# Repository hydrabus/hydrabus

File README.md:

HydraBus
========

HydraBus an open source multi-tool hardware

You can Buy HydraBus/HydraNFC Online: http://hydrabus.com/buy-online

Wiki Getting Started: https://github.com/hydrabus/hydrafw/wiki/Getting-Started-with-HydraBus

HydraFW official firmware for Hydrabus
========

Wiki for HydraFW: https://github.com/hydrabus/hydrafw/wiki

See https://github.com/hydrabus/hydrafw

To build hydrafw see instructions here: 
* Windows: https://github.com/hydrabus/hydrafw/wiki/how-to-build-flash-and-use-hydrafw-on-windows
* Linux: https://github.com/hydrabus/hydrafw/wiki/how-to-build-flash-and-use-hydrafw-on-linux

Official Micro Python port for HydraBus
========
See https://github.com/micropython/micropython
Tested with GCC ARM 4.9 2015q3(GNU_ARM_4_9_2015q3) 
* See https://github.com/hydrabus/hydrafw_hydranfc_shield_v2/wiki `How to Build/Flash/Use HydraFW` for more details

To build micropython for HydraBus do:

    git clone --recursive https://github.com/micropython/micropython
    cd micropython/ports/stm32
    make BOARD=HYDRABUS

* At end of build you shall have:
 * GEN build-HYDRABUS/firmware.dfu
 * GEN build-HYDRABUS/firmware.hex
* In order to flash the *.dfu follow steps here: https://github.com/hydrabus/hydrafw/wiki/Getting-Started-with-HydraBus

For more details on official micropython hydrabus port see: https://github.com/micropython/micropython/tree/master/ports/stm32/boards/HYDRABUS

Official Black Magic JTAG/SWD debugger port for HydraBus
========
See https://github.com/blacksphere/blackmagic.git

Before to build the firmware check this issue (as you need a new GCC ARM Compiler >=4.9): https://github.com/blacksphere/blackmagic/issues/128
Tested with GCC ARM 4.9 2015q3(GNU_ARM_4_9_2015q3)
* See working version for reference blackmagic_branch_hydrabus_Firmware 1.5-00319-g49390fe-dirty.zip:
  * https://github.com/hydrabus/hydrabus/files/11436416/blackmagic_branch_hydrabus_Firmware.1.5-00319-g49390fe-dirty.zip
* Note: Latest version of blackmagic have "Device failed enumeration" issue see https://github.com/hydrabus/hydrabus/issues/4
* See https://github.com/hydrabus/hydrafw_hydranfc_shield_v2/wiki `How to Build/Flash/Use HydraFW` for more details

To build Black Magic for HydraBus do:

    git clone --recursive https://github.com/blacksphere/blackmagic.git
    cd blackmagic
    make PROBE_HOST=hydrabus

* At end of build you shall have:
 * OBJCOPY blackmagic.bin
 * OBJCOPY blackmagic.hex
 * Creating blackmagic.dfu
* In order to flash the *.dfu follow steps here: https://github.com/bvernoux/hydrafw/wiki/Getting-Started-with-HydraBus

For more details on official blackmagic hydrabus port see:
https://github.com/blacksphere/blackmagic/tree/master/src/platforms/hydrabus

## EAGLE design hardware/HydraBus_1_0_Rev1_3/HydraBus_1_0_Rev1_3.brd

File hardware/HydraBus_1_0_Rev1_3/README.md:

HydraBus Schematic and Board CadSoft Eagle 6.x
========

This directory contains HydraBus Schematic and Board for CadSoft Eagle 6.x (free version works too)

HydraBus: Hardware license [CC BY-NC 4.0](https://creativecommons.org/licenses/by-nc/4.0/) (for commercial license contact info@hydrabus.com)

For more details on the hardware see also http://hydrabus.com/hydrabus-1-0-specifications

Revision 1.3 (vs Rev 1.2+)
- Modified the 2 microUSB to new ones which are more robust (HRO_U-F-M5DD-Y-L)
- Minor board routing improvement/optimization

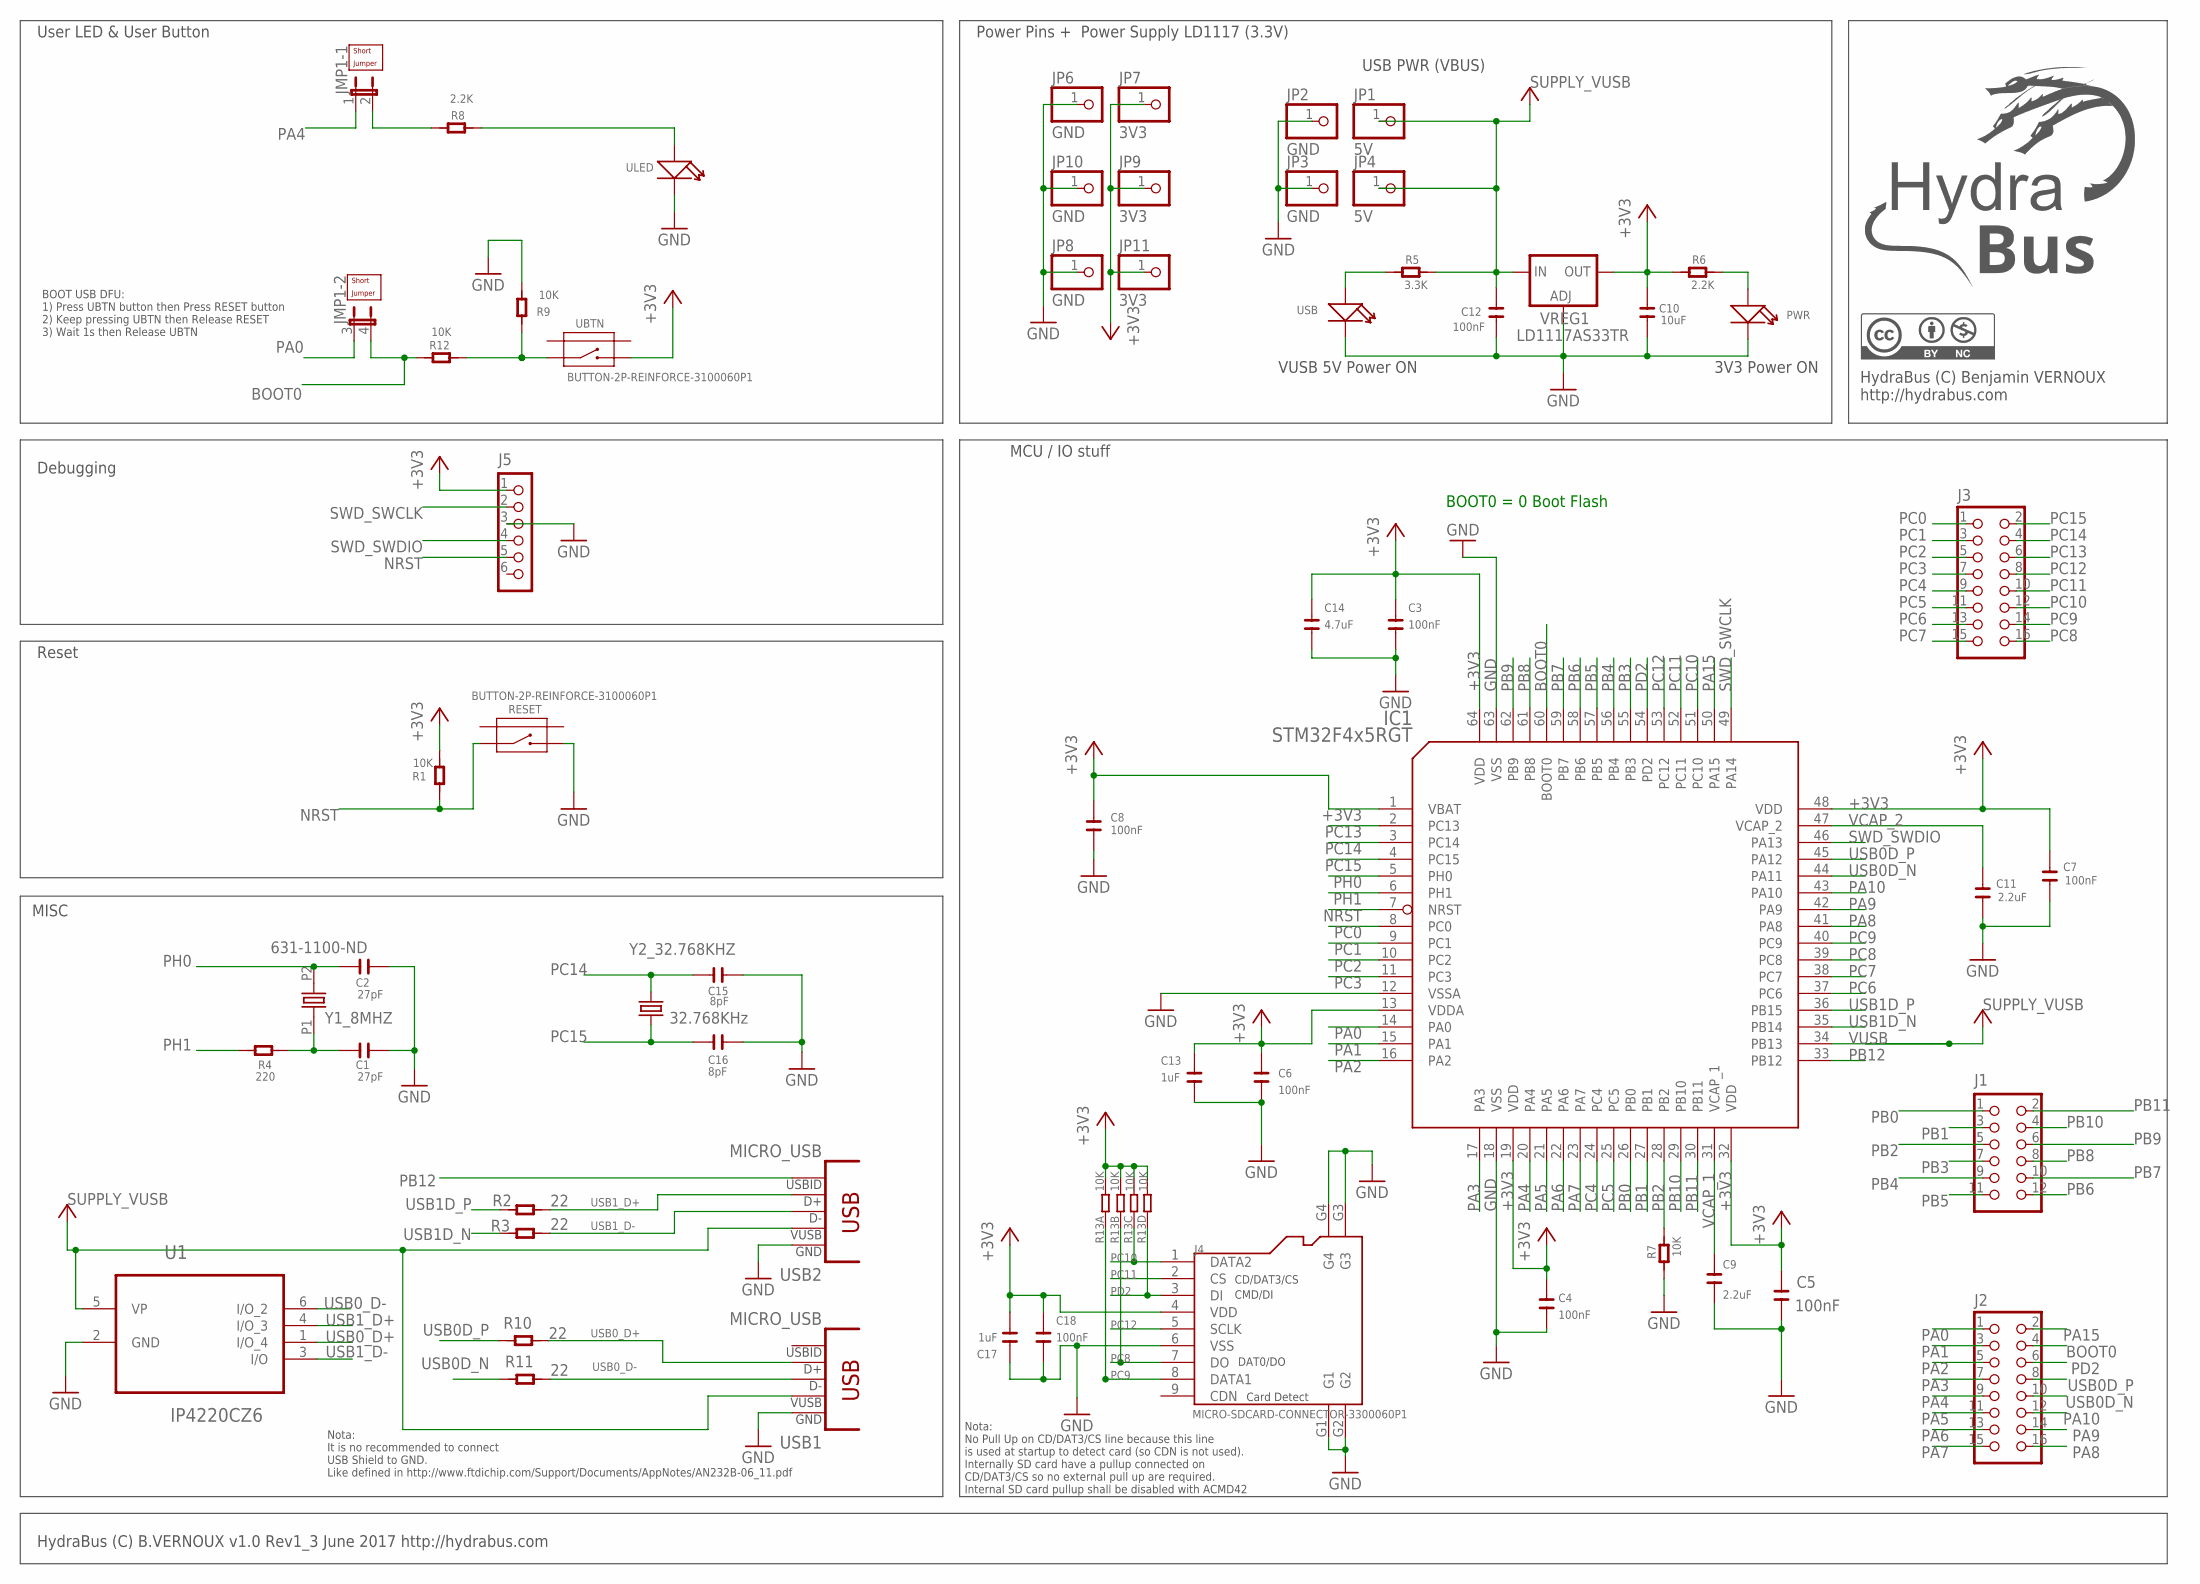
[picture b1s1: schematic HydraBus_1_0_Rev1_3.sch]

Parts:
C1, C2: 27pF; C0603
C3, C4, C5, C6, C7, C8, C12, C18: 100nF; C0603
C9, C11: 2.2uF; C0603
C10: 10uF; C0805
C13, C17: 1uF; C0603
C14: 4.7uF; C0603
C15, C16: 8pF; C0603
IC1: STM32F4x5RGT; LQFP64
J1: CON_HEADER_2X06; M2X6
J2, J3: CON_HEADER_2X08; M2X8
J4: MICRO-SDCARD-CONNECTOR-3300060P1; 9P-SMD-W-RING
J5: CON_HEADER_1X06-PTH; M1X6
JMP1: JP2QE; JP2Q
JMP_UBTN: SHORT-JUMPER-2P-3460440P1; 2P-2.54
JMP_ULED: SHORT-JUMPER-2P-3460440P1; 2P-2.54
JP1, JP4: 5V; 1X01
JP2, JP3, JP6, JP8, JP10: GND; 1X01
JP7, JP9, JP11: 3V3; 1X01
PWR: LED; LED0603
R1, R7, R9, R12: 10K; R0603
R2, R3, R10, R11: 22; R0603
R4: 220; R0603
R5: 3.3K; R0603
R6, R8: 2.2K; R0603
R13: 10K; R1206-8
RESET: BUTTON-2P-REINFORCE-3100060P1; 4P-SMD-7.0X3.5X3.5H-90D
U1: IP4220CZ6; SOT95P275X110-6N
UBTN: BUTTON-2P-REINFORCE-3100060P1; 4P-SMD-7.0X3.5X3.5H-90D
ULED: LED; LED0603
USB: LED; LED0603
USB1, USB2: MICRO_USB; MICRO_USB5+6P_SMD_0_65
VREG1: LD1117AS33TR; SOT223
Y1_8MHZ: 631-1100-ND; HC-49U-PTH
Y2_32.768KHZ: 32.768KHz; TC38H

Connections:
+3V3: C3.1, C4.1, C5.2, C6.1, C7.1, C8.1, C10.1, C13.1, C14.1, C17.2, C18.1, IC1.1 (VBAT), IC1.13 (VDDA), IC1.19 (VDD), IC1.32 (VDD), IC1.48 (VDD), IC1.64 (VDD), J4.4 (VDD), J5.1, JP7.1, JP9.1, JP11.1, R1.2, R6.2, R13.5 (2), R13.6 (2), R13.7 (2), R13.8 (2), UBTN.2, VREG1.4 (OUT)
BOOT0: IC1.60 (BOOT0), J2.4, JMP1.4 (2), R12.2
GND: C1.2, C2.2, C3.2, C4.2, C5.1, C6.2, C7.2, C8.2, C9.1, C10.2, C11.2, C12.2, C13.2, C14.2, C15.2, C16.2, C17.1, C18.2, IC1.12 (VSSA), IC1.18 (VSS), IC1.63 (VSS), J4.6 (VSS), J4.G1, J4.G2, J4.G3, J4.G4, J5.3, JP2.1, JP3.1, JP6.1, JP8.1, JP10.1, PWR.-, R7.2, R9.2, RESET.2, U1.2 (GND), ULED.-, USB.-, USB1.5 (GND), USB2.5 (GND), VREG1.1 (ADJ)
unnamed: C1.1, R4.1, Y1_8MHZ.P1 (1)
unnamed: JMP1.2, R8.2
unnamed: R9.1, R12.1, UBTN.1
unnamed: R8.1, ULED.+
unnamed: R5.2, USB.+
unnamed: PWR.+, R6.1
NRST: IC1.7 (NRST), J5.5, R1.1, RESET.1
PA0: IC1.14 (PA0), J2.1, JMP1.3 (1)
PA1: IC1.15 (PA1), J2.3
PA2: IC1.16 (PA2), J2.5
PA3: IC1.17 (PA3), J2.7
PA4: IC1.20 (PA4), J2.9, JMP1.1
PA5: IC1.21 (PA5), J2.11
PA6: IC1.22 (PA6), J2.13
PA7: IC1.23 (PA7), J2.15
PA8: IC1.41 (PA8), J2.16
PA9: IC1.42 (PA9), J2.14
PA10: IC1.43 (PA10), J2.12
PA15: IC1.50 (PA15), J2.2
PB0: IC1.26 (PB0), J1.1
PB1: IC1.27 (PB1), J1.3
PB2: IC1.28 (PB2), J1.5, R7.1
PB3: IC1.55 (PB3), J1.7
PB4: IC1.56 (PB4), J1.9
PB5: IC1.57 (PB5), J1.11
PB6: IC1.58 (PB6), J1.12
PB7: IC1.59 (PB7), J1.10
PB8: IC1.61 (PB8), J1.8
PB9: IC1.62 (PB9), J1.6
PB10: IC1.29 (PB10), J1.4
PB11: IC1.30 (PB11), J1.2
PB12: IC1.33 (PB12), USB2.4 (USBID)
PC0: IC1.8 (PC0), J3.1
PC1: IC1.9 (PC1), J3.3
PC2: IC1.10 (PC2), J3.5
PC3: IC1.11 (PC3), J3.7
PC4: IC1.24 (PC4), J3.9
PC5: IC1.25 (PC5), J3.11
PC6: IC1.37 (PC6), J3.13
PC7: IC1.38 (PC7), J3.15
PC8: IC1.39 (PC8), J3.16, J4.7 (DO), R13.2 (1)
PC9: IC1.40 (PC9), J3.14, J4.8 (DATA1), R13.1
PC10: IC1.51 (PC10), J3.12, J4.1 (DATA2), R13.3 (1)
PC11: IC1.52 (PC11), J3.10, J4.2 (CS)
PC12: IC1.53 (PC12), J3.8, J4.5 (SCLK)
PC13: IC1.2 (PC13), J3.6
PC14: C15.1, IC1.3 (PC14), J3.4, Y2_32.768KHZ.2
PC15: C16.1, IC1.4 (PC15), J3.2, Y2_32.768KHZ.1
PD2: IC1.54 (PD2), J2.6, J4.3 (DI), R13.4 (1)
PH0: C2.1, IC1.5 (PH0), Y1_8MHZ.P2 (2)
PH1: IC1.6 (PH1), R4.2
SWD_SWCLK: IC1.49 (PA14), J5.2
SWD_SWDIO: IC1.46 (PA13), J5.4
USB0D_N: IC1.44 (PA11), J2.10, R11.2
USB0D_P: IC1.45 (PA12), J2.8, R10.2
USB0_D+: R10.1, U1.1 (I/O_4), USB1.3 (D+)
USB0_D-: R11.1, U1.6 (I/O_2), USB1.2 (D-)
USB1D_N: IC1.35 (PB14), R3.2
USB1D_P: IC1.36 (PB15), R2.2
USB1_D+: R2.1, U1.4 (I/O_3), USB2.3 (D+)
USB1_D-: R3.1, U1.3 (I/O), USB2.2 (D-)
VCAP_1: C9.2, IC1.31 (VCAP_1)
VCAP_2: C11.1, IC1.47 (VCAP_2)
VUSB: C12.1, IC1.34 (PB13), JP1.1, JP4.1, R5.1, U1.5 (VP), USB1.1 (VUSB), USB2.1 (VUSB), VREG1.3 (IN)

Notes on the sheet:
Debugging
Power Pins + Power Supply LD1117 (3.3V)
MCU / IO stuff
MISC
Reset
BOOT0 = 0 Boot Flash
USB PWR (VBUS)
3V3 Power ON
VUSB 5V Power ON
HydraBus (C) B.VERNOUX v1.0 Rev1_3 June 2017 http://hydrabus.com
User LED & User Button
CD/DAT3/CS
CMD/DI
Card Detect
DAT0/DO
Nota: No Pull Up on CD/DAT3/CS line because this line is used at startup to detect card (so CDN is not used). Internally SD card have a pullup connected on CD/DAT3/CS so no external pull up are required. Internal SD card pullup shall be disabled with ACMD42
HydraBus (C) Benjamin VERNOUX http://hydrabus.com
Nota: It is no recommended to connect USB Shield to GND. Like defined in http://www.ftdichip.com/Support/Documents/AppNotes/AN232B-06_11.pdf
BOOT USB DFU: 1) Press UBTN button then Press RESET button 2) Keep pressing UBTN then Release RESET 3) Wait 1s then Release UBTN

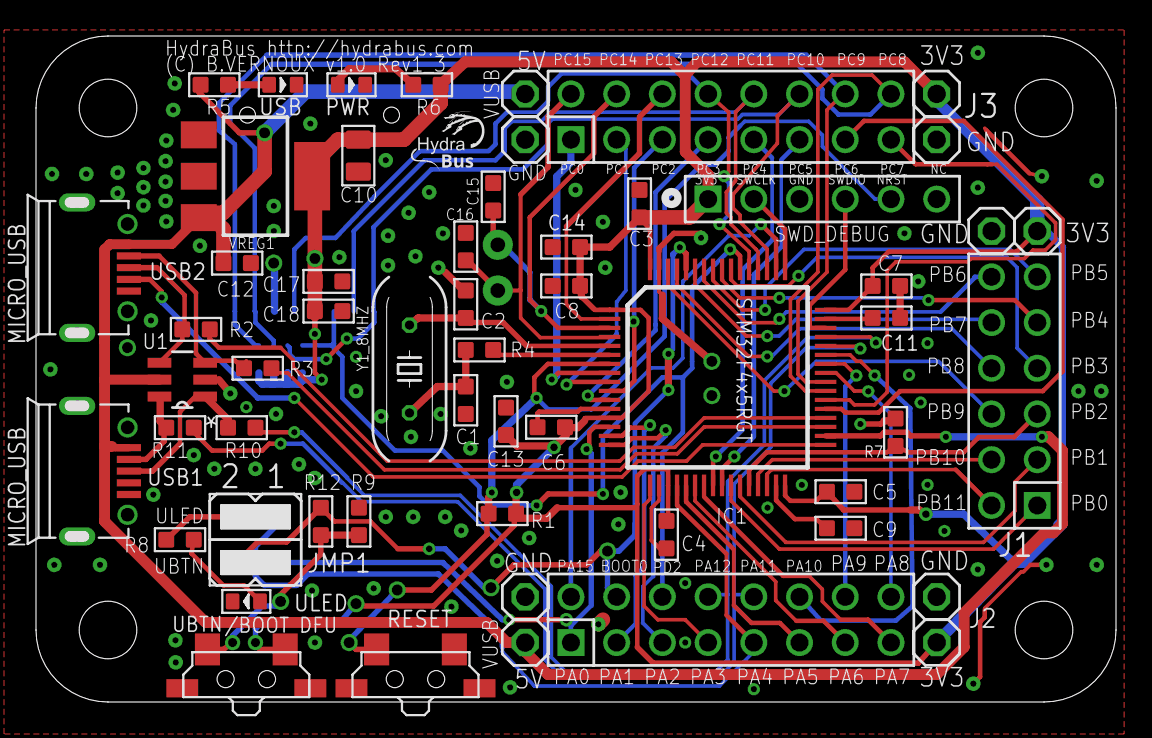
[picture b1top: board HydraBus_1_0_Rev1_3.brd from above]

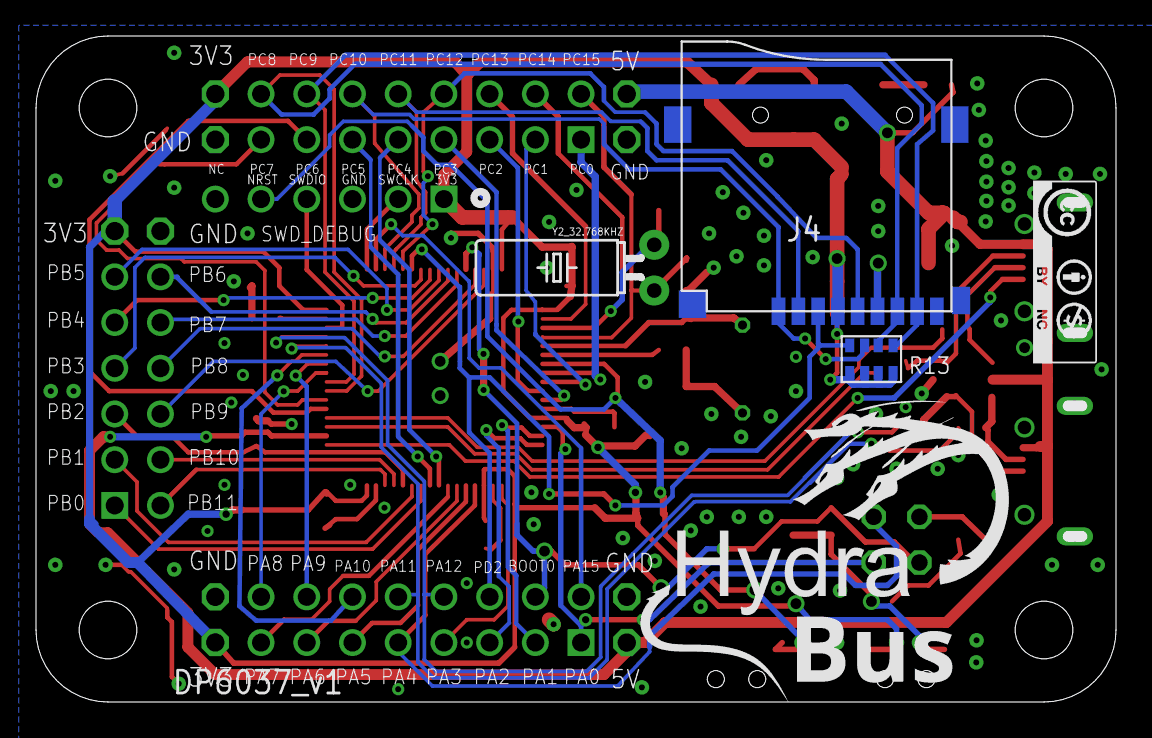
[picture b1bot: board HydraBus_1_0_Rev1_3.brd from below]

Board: 2 copper layers, 59.4 x 36.4 mm, 62 parts (3 on the bottom side), 67 nets.

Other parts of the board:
U$1: DP6037_V1

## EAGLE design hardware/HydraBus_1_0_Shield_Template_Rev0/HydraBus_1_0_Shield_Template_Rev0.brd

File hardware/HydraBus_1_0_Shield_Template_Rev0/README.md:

HydraBus 1_0 Shield Template CadSoft Eagle 6.x
========

This directory contains open source HydraBus 1_0 Shield Template Schematic and Board for CadSoft Eagle 6.x (free version works too)

HydraBus 1_0 Shield Template: Hardware licence CC BY-SA 4.0

For more details on the hardware see also http://hydrabus.com/?page_id=30

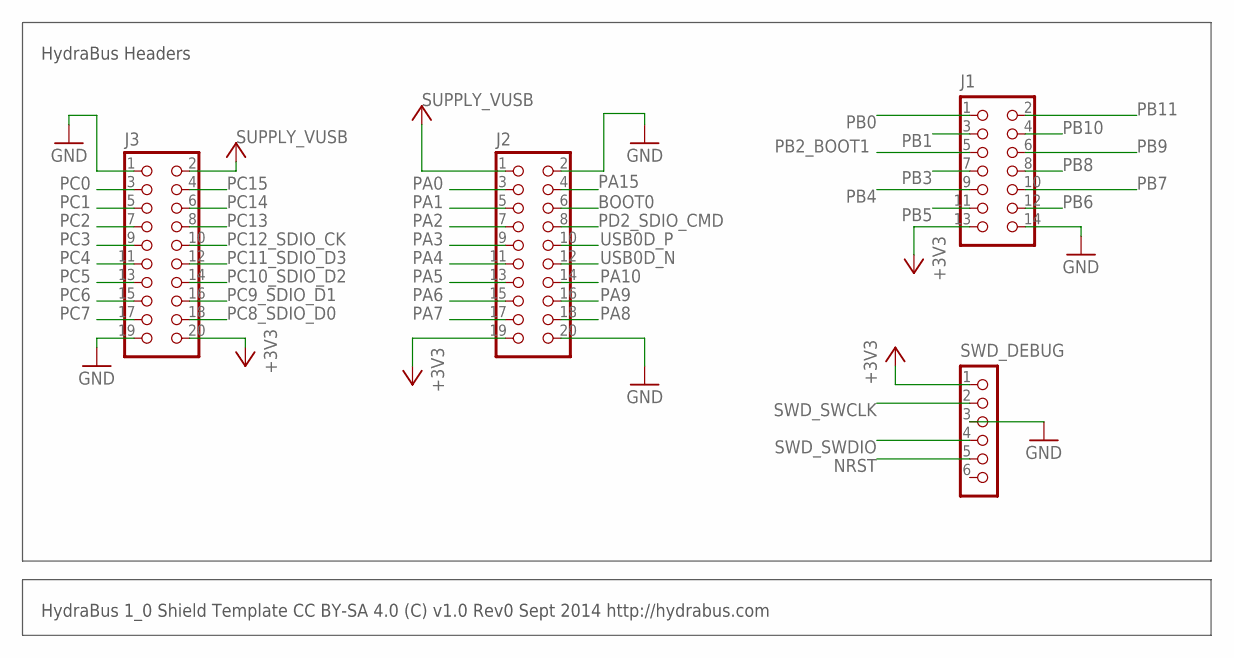
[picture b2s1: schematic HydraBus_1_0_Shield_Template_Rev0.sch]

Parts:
J1: HYDRABUS_SHIELD_CON_HEADER_2X07; HYDRABUS_SHIELD_M2X7
J2, J3: HYDRABUS_SHIELD_CON_HEADER_2X10; HYDRABUS_SHIELD_M2X10
SWD_DEBUG: HYDRABUS_SHIELD_CON_HEADER_1X06; HYDRABUS_SHIELD_M1X6

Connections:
+3V3: J1.13, J2.19, J3.20, SWD_DEBUG.1
BOOT0: J2.6
GND: J1.14, J2.2, J2.20, J3.1, J3.19, SWD_DEBUG.3
NRST: SWD_DEBUG.5
PA0: J2.3
PA1: J2.5
PA2: J2.7
PA3: J2.9
PA4: J2.11
PA5: J2.13
PA6: J2.15
PA7: J2.17
PA8: J2.18
PA9: J2.16
PA10: J2.14
PA15: J2.4
PB0: J1.1
PB1: J1.3
PB2_BOOT1: J1.5
PB3: J1.7
PB4: J1.9
PB5: J1.11
PB6: J1.12
PB7: J1.10
PB8: J1.8
PB9: J1.6
PB10: J1.4
PB11: J1.2
PC0: J3.3
PC1: J3.5
PC2: J3.7
PC3: J3.9
PC4: J3.11
PC5: J3.13
PC6: J3.15
PC7: J3.17
PC8_SDIO_D0: J3.18
PC9_SDIO_D1: J3.16
PC10_SDIO_D2: J3.14
PC11_SDIO_D3: J3.12
PC12_SDIO_CK: J3.10
PC13: J3.8
PC14: J3.6
PC15: J3.4
PD2_SDIO_CMD: J2.8
SWD_SWCLK: SWD_DEBUG.2
SWD_SWDIO: SWD_DEBUG.4
USB0D_N: J2.12
USB0D_P: J2.10
VUSB: J2.1, J3.2

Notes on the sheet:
HydraBus 1_0 Shield Template CC BY-SA 4.0 (C) v1.0 Rev0 Sept 2014 http://hydrabus.com
HydraBus Headers

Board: 2 copper layers, 4 parts (0 on the bottom side), 3 nets, no tracks yet.

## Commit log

2014-04-20 gitmodules update
2014-05-28 Update gitmodules
2014-05-28 Cleanup
2014-05-28 Cleanup gitmodule and added chibios 2.6.x
2014-06-02 HydraBus board
2014-06-22 Moved project/firmware to firmware directory
2014-09-11 HydraBus hardware files Eagle, PDF, xls ...
2014-09-11 Added MicroPython binary for HydraBus and instructions to flash it through USB DFU on HydraBus.
2014-09-11 Added board
2014-09-21 HydraFW first import version 0.1Beta
2014-09-21 Add picture for HydraBus to enter in USB DFU mode
2014-09-29 Update firmware from with last commit https://github.com/bvernoux/micropython/commit/41249e17c3a661dc36f49ff6156ce67a70466157
2014-09-30 HydraBus1.0 Sick Of Beige Case
2014-09-30 Windows XP, Vista, 7 and 8 drivers for HydraBus firmware USB CDC Virtual Serial Port.
2014-09-30 HydraBus1.0 Pin & Pin Assignment updated.
2014-10-01 Fix typo
2014-10-02 Added HydraBus Pins Assignment
2014-10-06 Add micropython firmware source as submodule.
2014-10-06 Add micropython firmware source as submodule and update with latest micropython.
2014-10-06 Cleanup Submodule micropython
2014-10-06 Add latest micropython as submodule
2014-10-06 Update micropython firmware to latest v1.3.3-31-g9c6f737
2014-10-07 Fixo typo thanks to Philippe Teuwen
    Update towards Philippe Teuwen wiki
    http://wiki.yobi.be/wiki/HydraNFC
2014-10-07 Fix for Debian... also exclude ModemManager thanks to Philippe Teuwen
2014-10-07 Fix typo thanks to Philippe Teuwen
    Update towards http://wiki.yobi.be/wiki/HydraNFC "Getting ready to use HydraBus" & "Using HydraBus"
2014-10-08 Cleanup, update configuration/conf and update microrl submodule.
2014-10-09 directory hydrafw deleted/replaced by submodule hydrafw
2014-10-10 Update hydrafw
2014-10-11 Added link to Wiki HydraFW
2014-10-13 Removed STM32F4_USB_DFU_Driver.zip
2014-10-22 Added HydraBus_1_0_HydraFW_Default_PinAssignment.odg/.pdf Fixed and update of HydraBus_1_0_PinAssignment.odg/.pdf
2014-10-22 Add A4 version of HydraBus_1_0_HydraFW_Default_PinAssignment
2014-10-22 Update link to latest hydrafw
2014-10-22 Updated submodule micropython to latest version
2014-10-22 update micropython firmware.dfu to latest version => Micro Python v1.3.3-113-g5fc42a6
2014-12-01 Added HydraBus Basic Pin Assignment
2014-12-26 Update micropython to latest Micro Python v1.3.3-340-gc55a4d8
2014-12-26 Update micropython to latest Micro Python v1.3.7-96-gc55a4d8
2014-12-26 Update hydrafw to latest version v0.4-beta-23-ge68b10a
2015-01-01 Updated Default Pin Assignment A4 and removed the old not A4.
2015-01-13 Added blackmagic port for HydraBus
2016-02-04 HydraBus v1.0 Rev1_2 Release (CadSoft Eagle v7.1 files + BOM + Schematic + Gerber)
2016-04-20 Update Black Magic official hydrabus port
2016-04-22 removed firmware link (obsolete)
2016-04-22 removed firmware link/submodule (obsolete)
2016-05-31 Add HydraBus_1_0_Shield_Template_Rev0 Kicad link
2016-12-06 HydraBus V1.0 Rev1.2+
2016-12-18 Update of links replaced bvernoux to hydrabus
2017-03-27 Create LICENSE
2017-08-03 HydraBus V1.0 Rev1.3
2018-10-03 Update official micropython hydrabus port link
2018-12-29 Updated pin assignment diagrams
2018-12-29 Removed GND/VCC arrows
2019-12-27 Updated 26 Dec 2019 with https://www.seeedstudio.com/opl.html
2020-05-14 Import HydraBus v1.0 Rev1.4 done with KiCad (5.1.5)-2
2020-05-14 Update adding HydraBus_1_0_Rev1_4
2020-08-29 Update HydraBus_board.jpg with latest HydraBus v1.0 Rev1.4 board photo
2024-01-01 Add HydraBus v1.0 Rev1.5 Schematic/Board Hardware license CC BY-NC 4.0 (KiCad 6.0.11) Update HydraBus_1_0_HydraFW_Basic_PinAssignment & HydraBus_1_0_HydraFW_Default_PinAssignment_A4 with latest Hydra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
2024-01-01 Update README.md with pictures with latest HydraBus v1.0 Rev1.5 board (USB Type C)
2024-01-03 Minor fixes / improvements on Default & Basic PinAssignment
2024-03-16 Add HydraBus_v1_0_Rev1_SoBv1_DP6037-Top_Bottom (Top is same as Bottom) in DXF & STL format
